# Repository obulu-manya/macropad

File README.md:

# Macropad

A compact PCB design created using **KiCad** as part of my PCB design learning journey. This project covers the complete process from schematic design to PCB layout and preparing files for PCB manufacturing.

---

## About

The goal of this project was to understand the complete PCB design workflow using KiCad. It includes creating the schematic, designing the PCB layout, routing the board, checking for design errors, and generating manufacturing files.

This project helped me gain practical experience in designing a PCB from start to finish.

---

## Travel Purpose

A compact macropad can be a useful travel companion for people who work on the go. It can be used to create custom shortcuts for frequently used applications, making everyday tasks faster while travelling with a laptop or tablet.

Its portable size also makes it suitable for remote work, study, and travel setups where desk space is limited.

---

## Tools Used

- KiCad

---

## Project Workflow

- Created the schematic
- Designed the PCB layout
- Routed the PCB traces
- Performed Design Rule Check (DRC)
- Generated Gerber files for manufacturing

---

## Project Files

### Design Files

```text
macropad obulu.kicad_sch
macropad obulu.kicad_pcb
macropad obulu.kicad_pro
macropad obulu.kicad_prl
```

### Gerber Files

```text
macropad obulu-F_Cu.gbr
macropad obulu-B_Cu.gbr
macropad obulu-F_Mask.gbr
macropad obulu-F_Paste.gbr
macropad obulu-B_Paste.gbr
macropad obulu-F_Silkscreen.gbr
macropad obulu-B_Silkscreen.gbr
macropad obulu-Edge_Cuts.gbr
macropad obulu-job.gbrjob
```

---

## What I Learned

- Schematic design using KiCad
- PCB layout and routing
- Design Rule Check (DRC)
- Gerber file generation
- PCB manufacturing workflow

---

## Project Preview

Add images of:

- Schematic
- PCB Layout
- 3D PCB View
- Final PCB (if manufactured)

---

This project was created as part of my learning in PCB design using KiCad.
https://github.com/obulu-manya/macropad.git

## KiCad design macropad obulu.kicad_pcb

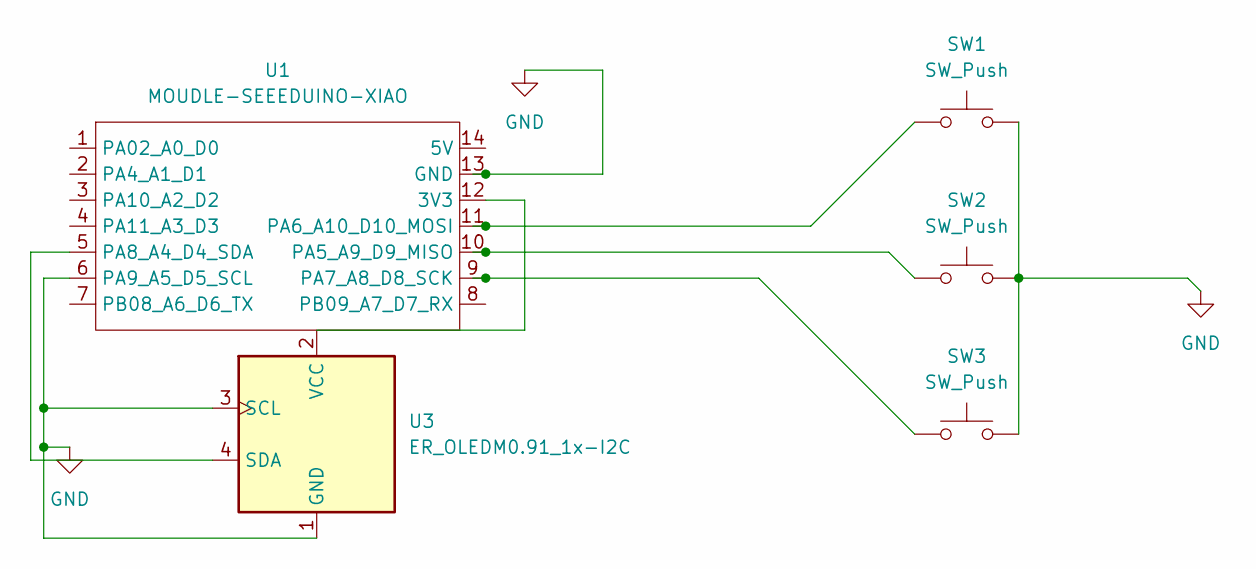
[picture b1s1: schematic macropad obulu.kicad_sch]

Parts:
SW1, SW2, SW3: SW_Push; SW_Cherry_MX_1.00u_PCB
U1: MOUDLE-SEEEDUINO-XIAO; XIAO-Generic-Hybrid-14P-2.54-21X17.8MM
U3: ER_OLEDM0.91_1x-I2C

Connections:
GND: SW1.2, SW2.2, SW3.2, U1.6 (PA9_A5_D5_SCL), U1.13 (GND), U3.1 (GND), U3.3 (SCL)
unnamed: U1.12 (3V3), U3.2 (VCC)
unnamed: SW2.1, U1.10 (PA5_A9_D9_MISO)
unnamed: SW1.1, U1.11 (PA6_A10_D10_MOSI)
unnamed: SW3.1, U1.9 (PA7_A8_D8_SCK)
unnamed: U1.5 (PA8_A4_D4_SDA), U3.4 (SDA)

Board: 2 copper layers, 5 parts (0 on the bottom side), 6 nets, no tracks yet.
